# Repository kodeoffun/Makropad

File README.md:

hey! ho!
My first project using CAD software!!
Fusion360 and kiCAD was a fun journey to learn!
This is a 8 switch + 1 button & 1 rotary encoder macro pad + an OLED display and easter eggs in the PCB :)

^^  
Lid will be screwed on  

BOM:
- 8x Cherry MX Switches
- 8x DSA Keycaps
- 8x 1N4148 Diodes
- 1x 0.91" 128x32 OLED Display
- 1x EC11 Rotary Encoder
- 1x XIAO RP2040
- 1x Case  (1 Lid and 1 Body 3d printed)

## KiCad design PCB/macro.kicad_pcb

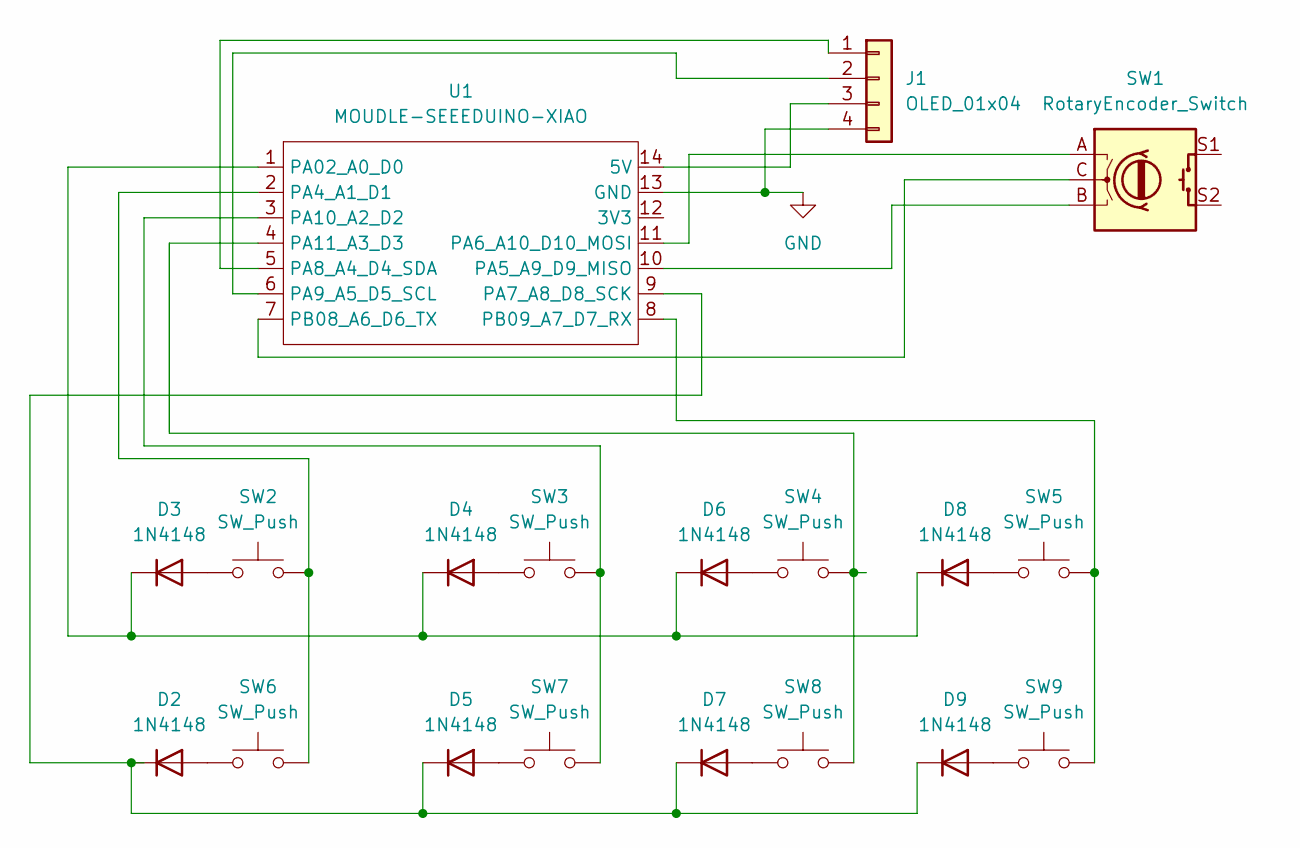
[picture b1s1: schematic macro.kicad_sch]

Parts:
D2, D3, D4, D5, D6, D7, D8, D9: 1N4148; D_DO-35_SOD27_P7.62mm_Horizontal
J1: OLED_01x04; PinHeader_1x04_P2.54mm_Vertical
SW1: RotaryEncoder_Switch; RotaryEncoder_Alps_EC11E-Switch_Vertical_H20mm
SW2, SW3, SW4, SW5, SW6, SW7, SW8, SW9: SW_Push; SW_Cherry_MX_1.00u_PCB
U1: MOUDLE-SEEEDUINO-XIAO; XIAO-Generic-Hybrid-14P-2.54-21X17.8MM

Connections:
GND: J1.4, U1.13 (GND)
unnamed: D2.2 (A), SW6.1
unnamed: D2.1 (K), D5.1 (K), D7.1 (K), D9.1 (K), U1.9 (PA7_A8_D8_SCK)
unnamed: D3.2 (A), SW2.1
unnamed: D3.1 (K), D4.1 (K), D6.1 (K), D8.1 (K), U1.1 (PA02_A0_D0)
unnamed: D4.2 (A), SW3.1
unnamed: D5.2 (A), SW7.1
unnamed: D6.2 (A), SW4.1
unnamed: D7.2 (A), SW8.1
unnamed: D8.2 (A), SW5.1
unnamed: D9.2 (A), SW9.1
unnamed: J1.1, U1.5 (PA8_A4_D4_SDA)
unnamed: J1.2, U1.6 (PA9_A5_D5_SCL)
unnamed: J1.3, U1.14 (5V)
unnamed: SW2.2, SW6.2, U1.2 (PA4_A1_D1)
unnamed: SW1.B, U1.10 (PA5_A9_D9_MISO)
unnamed: SW1.A, U1.11 (PA6_A10_D10_MOSI)
unnamed: SW3.2, SW7.2, U1.3 (PA10_A2_D2)
unnamed: SW4.2, SW8.2, U1.4 (PA11_A3_D3)
unnamed: SW1.C, U1.7 (PB08_A6_D6_TX)
unnamed: SW5.2, SW9.2, U1.8 (PB09_A7_D7_RX)

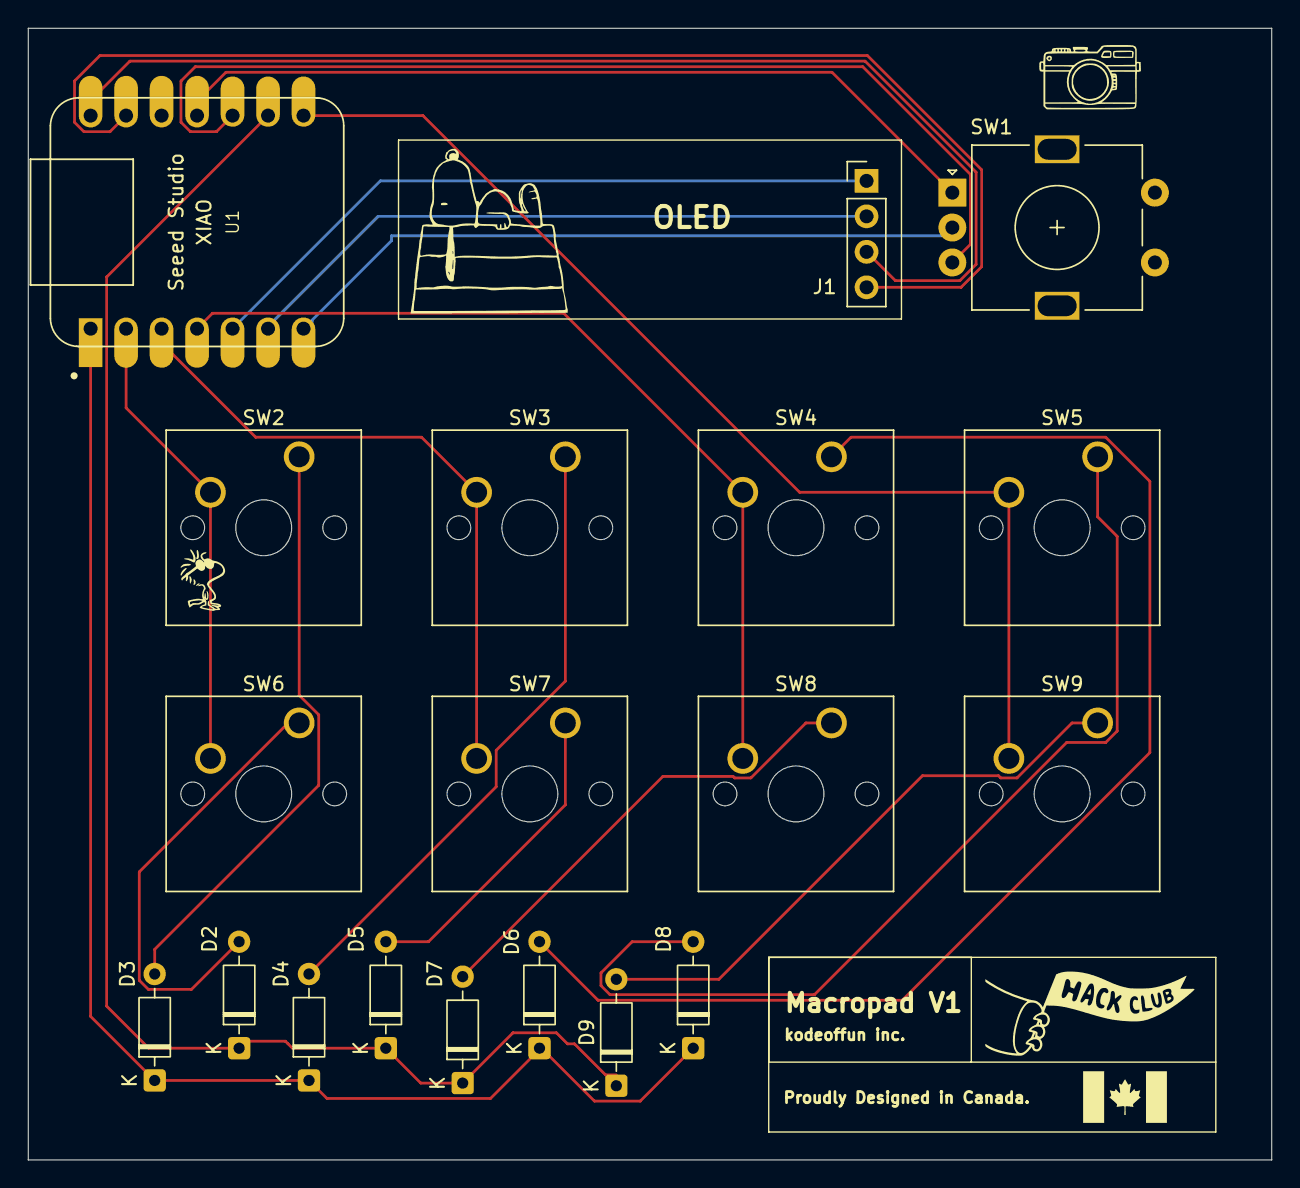
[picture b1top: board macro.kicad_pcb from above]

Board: 2 copper layers, 89.0 x 81.0 mm, 19 parts (0 on the bottom side), 21 nets.
